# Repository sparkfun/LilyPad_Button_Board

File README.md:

SparkFun LilyPad Button Board
========================================

[*SparkFun LilyPad Button Board (DEV-08776)*](https://www.sparkfun.com/products/8776)

We designed this board to give the user a low profile button without any sharp edges. 
Button closes when you push it and opens when you release (momentary push button).

Repository Contents
-------------------
* **/Hardware** - All Eagle design files (.brd, .sch)

Documentation
-------------------
* **[Hookup Guide](https://learn.sparkfun.com/tutorials/lilypad-buttons-and-switches)**

License Information
-------------------

This product is _**open source**_! 

Please review the LICENSE.md file for license information. 

If you have any questions or concerns on licensing, please contact techsupport@sparkfun.com.

Distributed as-is; no warranty is given.

- Your friends at SparkFun.

_<COLLABORATION CREDIT>_

_Note: A portion of this sale is given back to Dr. Leah Buechley for continued development and education of e-textiles._

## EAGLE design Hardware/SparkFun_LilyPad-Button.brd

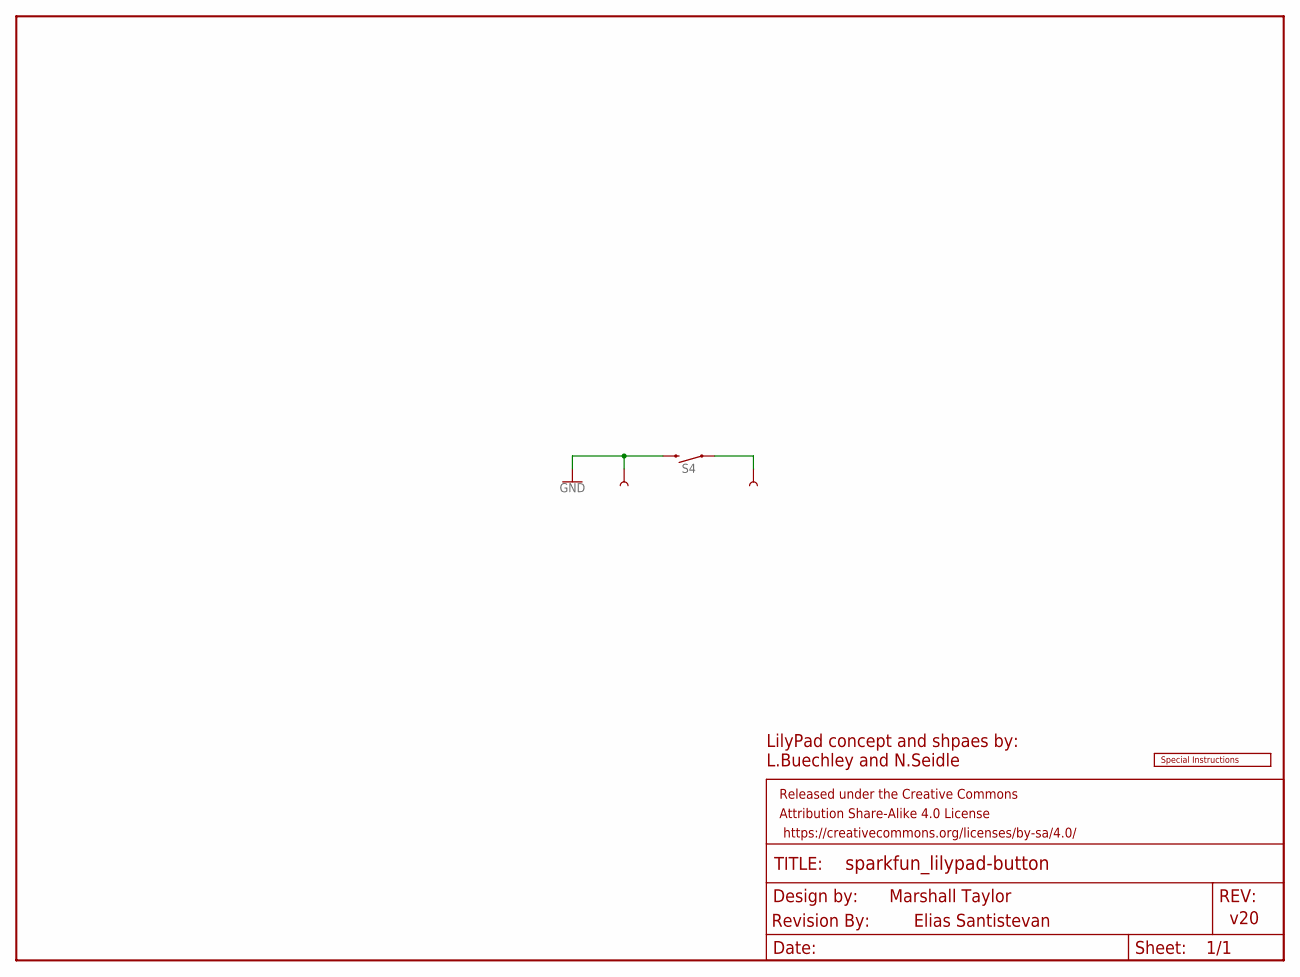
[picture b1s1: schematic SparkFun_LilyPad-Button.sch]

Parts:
FRAME2: FRAME-LETTER; CREATIVE_COMMONS
JP12, JP13: SEWTAP_MEDIUM-2SIDE; PETAL-MEDIUM-2SIDE
S4: MOMENTARY-SWITCH-SPST-SMD-5.2-REDUNDANT; TACTILE_SWITCH_SMD_5.2MM
U$1: SPECIAL_INSTRUCTIONS-ORDERING; ORDERING_INSTRUCTIONS

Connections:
D4: JP12.1, S4.1, S4.2 (1)
GND: JP13.1, S4.3 (2), S4.4 (2)

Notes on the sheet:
Marshall Taylor
v20
Elias Santistevan
Revision By:
LilyPad concept and shpaes by: L.Buechley and N.Seidle

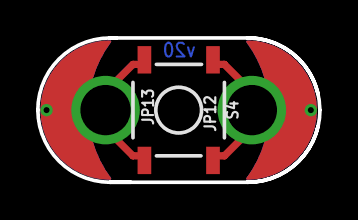
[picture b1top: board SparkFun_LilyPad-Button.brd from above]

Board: 2 copper layers, 15.7 x 8.0 mm, 6 parts (1 on the bottom side), 2 nets.

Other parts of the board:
U$45: LOGO-L

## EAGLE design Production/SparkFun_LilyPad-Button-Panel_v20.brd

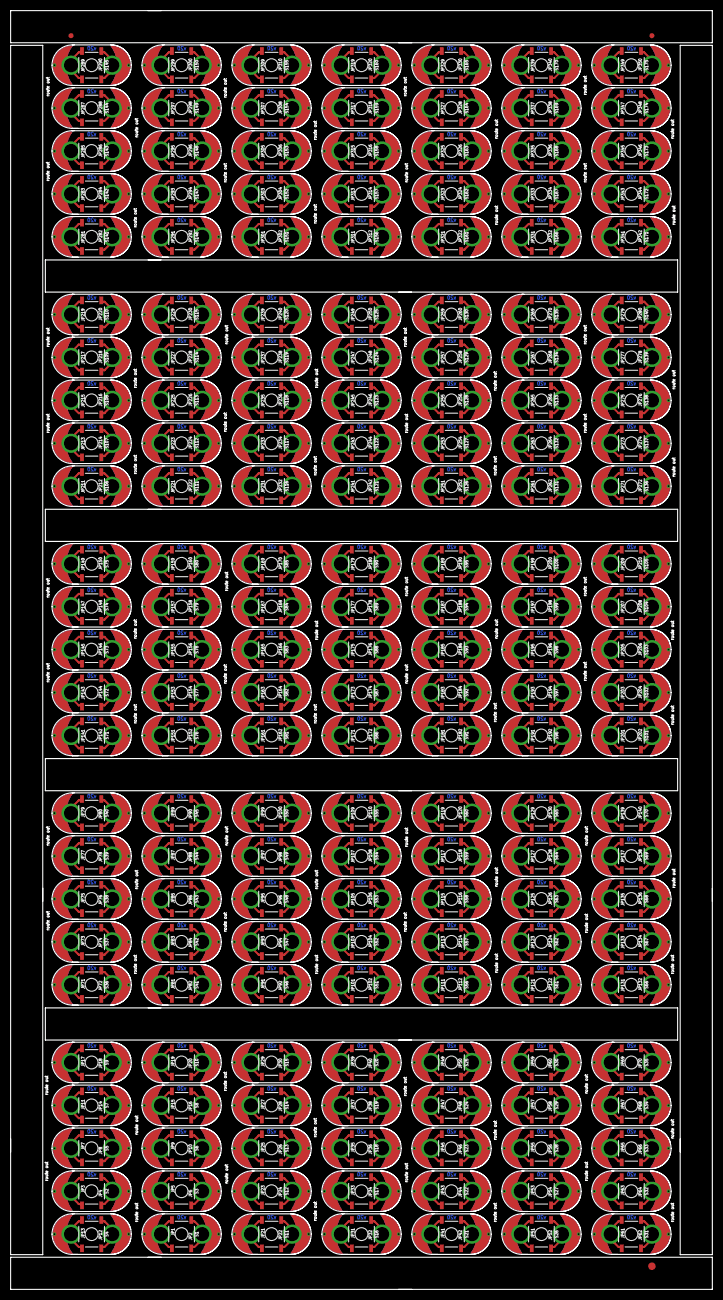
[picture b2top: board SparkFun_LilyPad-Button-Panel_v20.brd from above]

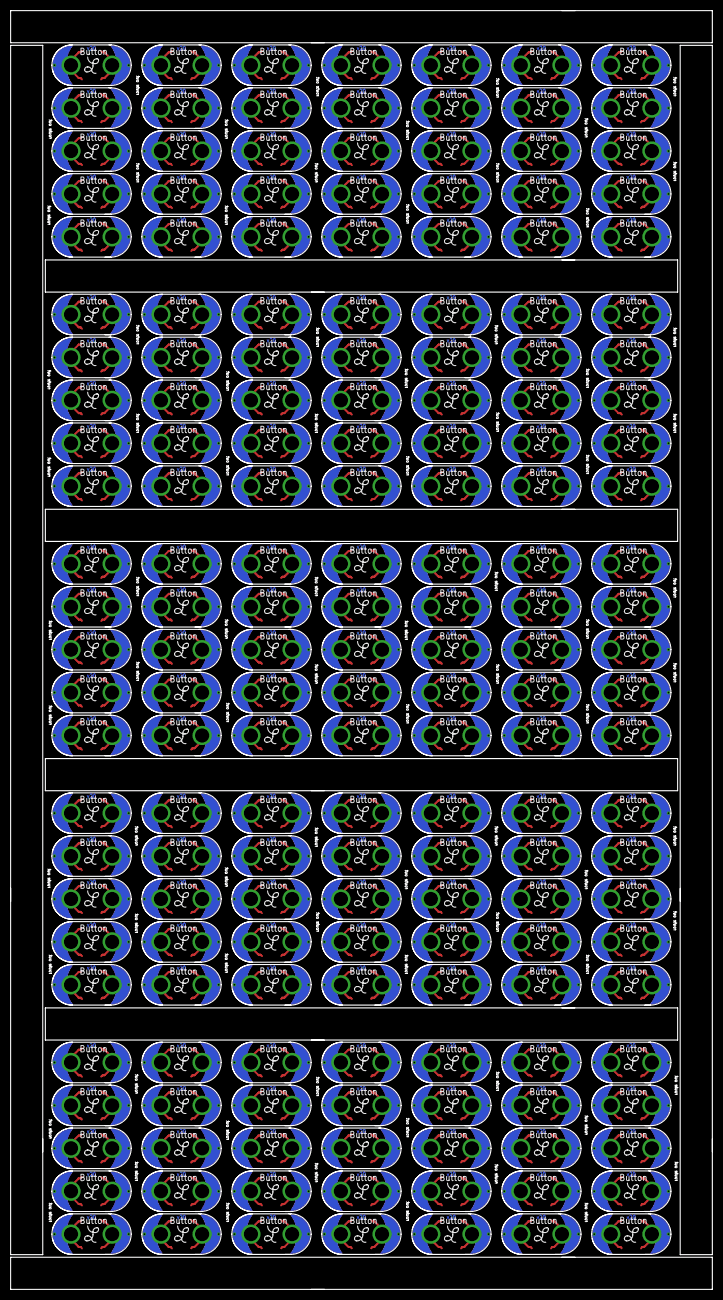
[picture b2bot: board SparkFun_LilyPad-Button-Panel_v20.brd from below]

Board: 2 copper layers, 138.7 x 252.7 mm, 703 parts (175 on the bottom side), 350 nets.

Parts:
E$1: FIDUCIAL-1.5X3
E$15, E$16: FIDUCIAL-1X2
JP1, JP2, JP3, JP4, JP5, JP6, JP7, JP8, JP9, JP10, JP11, JP12, JP13, JP14, JP15, JP16, JP17, JP18, JP19, JP20, JP21, JP22, JP23, JP24, JP25, JP26, JP27, JP28, JP29, JP30, JP31, JP32, JP33, JP34, JP35, JP36, JP37, JP38, JP39, JP40, JP41, JP42, JP43, JP44, JP45, JP46, JP47, JP48, JP49, JP50, JP51, JP52, JP53, JP54, JP55, JP56, JP57, JP58, JP59, JP60, JP61, JP62, JP63, JP64, JP65, JP66, JP67, JP68, JP69, JP70, JP71, JP72, JP73, JP74, JP75, JP76, JP77, JP78, JP79, JP80, JP81, JP82, JP83, JP84, JP85, JP86, JP87, JP88, JP89, JP90, JP91, JP92, JP93, JP94, JP95, JP96, JP97, JP98, JP99, JP100, JP101, JP102, JP103, JP104, JP105, JP106, JP107, JP108, JP109, JP110, JP111, JP112, JP113, JP114, JP115, JP116, JP117, JP118, JP119, JP120, JP121, JP122, JP123, JP124, JP125, JP126, JP127, JP128, JP129, JP130, JP131, JP132, JP133, JP134, JP135, JP136, JP137, JP138, JP139, JP140, JP141, JP142, JP143, JP144, JP145, JP146, JP147, JP148, JP149, JP150, JP151, JP152, JP153, JP154, JP155, JP156, JP157, JP158, JP159, JP160, JP161, JP162, JP163, JP164, JP165, JP166, JP167, JP168, JP169, JP170, JP171, JP172, JP173, JP174, JP175, JP176, JP177, JP178, JP179, JP180, JP181, JP182, JP183, JP184, JP185, JP186, JP187, JP188, JP189, JP190, JP191, JP192, JP193, JP194, JP195, JP196, JP197, JP198, JP199, JP200, JP201, JP202, JP203, JP204, JP205, JP206, JP207, JP208, JP209, JP210, JP211, JP212, JP213, JP214, JP215, JP216, JP217, JP218, JP219, JP220, JP221, JP222, JP223, JP224, JP225, JP226, JP227, JP228, JP229, JP230, JP231, JP232, JP233, JP234, JP235, JP236, JP237, JP238, JP239, JP240, JP241, JP242, JP243, JP244, JP245, JP246, JP247, JP248, JP249, JP250, JP251, JP252, JP253, JP254, JP255, JP256, JP257, JP258, JP259, JP260, JP261, JP262, JP263, JP264, JP265, JP266, JP267, JP268, JP269, JP270, JP271, JP272, JP273, JP274, JP275, JP276, JP277, JP278, JP279, JP280, JP281, JP282, JP283, JP284, JP285, JP286, JP287, JP288, JP289, JP290, JP291, JP292, JP293, JP294, JP295, JP296, JP297, JP298, JP299, JP300, JP301, JP302, JP303, JP304, JP305, JP306, JP307, JP308, JP309, JP310, JP311, JP312, JP313, JP314, JP315, JP316, JP317, JP318, JP319, JP320, JP321, JP322, JP323, JP324, JP325, JP326, JP327, JP328, JP329, JP330, JP331, JP332, JP333, JP334, JP335, JP336, JP337, JP338, JP339, JP340, JP341, JP342, JP343, JP344, JP345, JP346, JP347, JP348, JP349, JP350: SEWTAP_MEDIUM-2SIDE; PETAL-MEDIUM-2SIDE
S1, S2, S3, S4, S5, S6, S7, S8, S9, S10, S11, S12, S13, S14, S15, S16, S17, S18, S19, S20, S21, S22, S23, S24, S25, S26, S27, S28, S29, S30, S31, S32, S33, S34, S35, S36, S37, S38, S39, S40, S41, S42, S43, S44, S45, S46, S47, S48, S49, S50, S51, S52, S53, S54, S55, S56, S57, S58, S59, S60, S61, S62, S63, S64, S65, S66, S67, S68, S69, S70, S71, S72, S73, S74, S75, S76, S77, S78, S79, S80, S81, S82, S83, S84, S85, S86, S87, S88, S89, S90, S91, S92, S93, S94, S95, S96, S97, S98, S99, S100, S101, S102, S103, S104, S105, S106, S107, S108, S109, S110, S111, S112, S113, S114, S115, S116, S117, S118, S119, S120, S121, S122, S123, S124, S125, S126, S127, S128, S129, S130, S131, S132, S133, S134, S135, S136, S137, S138, S139, S140, S141, S142, S143, S144, S145, S146, S147, S148, S149, S150, S151, S152, S153, S154, S155, S156, S157, S158, S159, S160, S161, S162, S163, S164, S165, S166, S167, S168, S169, S170, S171, S172, S173, S174, S175: MOMENTARY-SWITCH-SPST-SMD-5.2-REDUNDANT; TACTILE_SWITCH_SMD_5.2MM
U$1, U$2, U$3, U$4, U$5, U$6, U$7, U$8, U$9, U$10, U$11, U$12, U$13, U$14, U$15, U$16, U$17, U$18, U$19, U$20, U$21, U$22, U$23, U$24, U$25, U$26, U$27, U$28, U$29, U$30, U$31, U$32, U$33, U$34, U$35, U$36, U$37, U$38, U$39, U$40, U$41, U$42, U$43, U$44, U$45, U$46, U$47, U$48, U$49, U$50, U$51, U$52, U$53, U$54, U$55, U$56, U$57, U$58, U$59, U$60, U$61, U$62, U$63, U$64, U$65, U$66, U$67, U$68, U$69, U$70, U$71, U$72, U$73, U$74, U$75, U$76, U$77, U$78, U$79, U$80, U$81, U$82, U$83, U$84, U$85, U$86, U$87, U$88, U$89, U$90, U$91, U$92, U$93, U$94, U$95, U$96, U$97, U$98, U$99, U$100, U$101, U$102, U$103, U$104, U$105, U$106, U$107, U$108, U$109, U$110, U$111, U$112, U$113, U$114, U$115, U$116, U$117, U$118, U$119, U$120, U$121, U$122, U$123, U$124, U$125, U$126, U$127, U$128, U$129, U$130, U$131, U$132, U$133, U$134, U$135, U$136, U$137, U$138, U$139, U$140, U$141, U$142, U$143, U$144, U$145, U$146, U$147, U$148, U$149, U$150, U$151, U$152, U$153, U$154, U$155, U$156, U$157, U$158, U$159, U$160, U$161, U$162, U$163, U$164, U$165, U$166, U$167, U$168, U$169, U$170, U$171, U$172, U$173, U$174, U$175: LOGO-L

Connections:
D1: JP2.1, S1.1, S1.2
D2: JP4.1, S2.1, S2.2
D3: JP6.1, S3.1, S3.2
D4: JP12.1, S4.1, S4.2
D5: JP8.1, S5.1, S5.2
D6: JP10.1, S6.1, S6.2
D7: JP14.1, S7.1, S7.2
D8: JP16.1, S8.1, S8.2
D9: JP18.1, S9.1, S9.2
D10: JP20.1, S10.1, S10.2
D11: JP22.1, S11.1, S11.2
D12: JP24.1, S12.1, S12.2
D13: JP26.1, S13.1, S13.2
D14: JP28.1, S14.1, S14.2
D15: JP30.1, S15.1, S15.2
D16: JP32.1, S16.1, S16.2
D17: JP34.1, S17.1, S17.2
D18: JP36.1, S18.1, S18.2
D19: JP38.1, S19.1, S19.2
D20: JP40.1, S20.1, S20.2
D21: JP42.1, S21.1, S21.2
D22: JP44.1, S22.1, S22.2
D23: JP46.1, S23.1, S23.2
D24: JP48.1, S24.1, S24.2
D25: JP50.1, S25.1, S25.2
D26: JP52.1, S26.1, S26.2
D27: JP54.1, S27.1, S27.2
D28: JP56.1, S28.1, S28.2
D29: JP58.1, S29.1, S29.2
D30: JP60.1, S30.1, S30.2
D31: JP62.1, S31.1, S31.2
D32: JP64.1, S32.1, S32.2
D33: JP66.1, S33.1, S33.2
D34: JP68.1, S34.1, S34.2
D35: JP70.1, S35.1, S35.2
D36: JP72.1, S36.1, S36.2
D37: JP74.1, S37.1, S37.2
D38: JP76.1, S38.1, S38.2
D39: JP78.1, S39.1, S39.2
D40: JP80.1, S40.1, S40.2
D41: JP82.1, S41.1, S41.2
D42: JP84.1, S42.1, S42.2
D43: JP86.1, S43.1, S43.2
D44: JP88.1, S44.1, S44.2
D45: JP90.1, S45.1, S45.2
D46: JP92.1, S46.1, S46.2
D47: JP94.1, S47.1, S47.2
D48: JP96.1, S48.1, S48.2
D49: JP98.1, S49.1, S49.2
D50: JP100.1, S50.1, S50.2
D51: JP102.1, S51.1, S51.2
D52: JP104.1, S52.1, S52.2
D53: JP106.1, S53.1, S53.2
D54: JP108.1, S54.1, S54.2
D55: JP110.1, S55.1, S55.2
D56: JP112.1, S56.1, S56.2
D57: JP114.1, S57.1, S57.2
D58: JP116.1, S58.1, S58.2
D59: JP118.1, S59.1, S59.2
D60: JP120.1, S60.1, S60.2
D61: JP122.1, S61.1, S61.2
D62: JP124.1, S62.1, S62.2
D63: JP126.1, S63.1, S63.2
D64: JP128.1, S64.1, S64.2
D65: JP130.1, S65.1, S65.2
D66: JP132.1, S66.1, S66.2
D67: JP134.1, S67.1, S67.2
D68: JP136.1, S68.1, S68.2
D69: JP138.1, S69.1, S69.2
D70: JP140.1, S70.1, S70.2
D71: JP142.1, S71.1, S71.2
D72: JP144.1, S72.1, S72.2
D73: JP146.1, S73.1, S73.2
D74: JP148.1, S74.1, S74.2
D75: JP150.1, S75.1, S75.2
D76: JP152.1, S76.1, S76.2
D77: JP154.1, S77.1, S77.2
D78: JP156.1, S78.1, S78.2
D79: JP158.1, S79.1, S79.2
D80: JP160.1, S80.1, S80.2
D81: JP162.1, S81.1, S81.2
D82: JP164.1, S82.1, S82.2
D83: JP166.1, S83.1, S83.2
D84: JP168.1, S84.1, S84.2
D85: JP170.1, S85.1, S85.2
D86: JP172.1, S86.1, S86.2
D87: JP174.1, S87.1, S87.2
D88: JP176.1, S88.1, S88.2
D89: JP178.1, S89.1, S89.2
D90: JP180.1, S90.1, S90.2
D91: JP182.1, S91.1, S91.2
D92: JP184.1, S92.1, S92.2
D93: JP186.1, S93.1, S93.2
D94: JP188.1, S94.1, S94.2
D95: JP190.1, S95.1, S95.2
D96: JP192.1, S96.1, S96.2
D97: JP194.1, S97.1, S97.2
D98: JP196.1, S98.1, S98.2
D99: JP198.1, S99.1, S99.2
D100: JP200.1, S100.1, S100.2
D101: JP202.1, S101.1, S101.2
D102: JP204.1, S102.1, S102.2
D103: JP206.1, S103.1, S103.2
D104: JP208.1, S104.1, S104.2
D105: JP210.1, S105.1, S105.2
D106: JP212.1, S106.1, S106.2
D107: JP214.1, S107.1, S107.2
D108: JP216.1, S108.1, S108.2
D109: JP218.1, S109.1, S109.2
D110: JP220.1, S110.1, S110.2
D111: JP222.1, S111.1, S111.2
D112: JP224.1, S112.1, S112.2
D113: JP226.1, S113.1, S113.2
D114: JP228.1, S114.1, S114.2
D115: JP230.1, S115.1, S115.2
D116: JP232.1, S116.1, S116.2
D117: JP234.1, S117.1, S117.2
D118: JP236.1, S118.1, S118.2
D119: JP238.1, S119.1, S119.2
D120: JP240.1, S120.1, S120.2
D121: JP242.1, S121.1, S121.2
D122: JP244.1, S122.1, S122.2
D123: JP246.1, S123.1, S123.2
D124: JP248.1, S124.1, S124.2
D125: JP250.1, S125.1, S125.2
D126: JP252.1, S126.1, S126.2
D127: JP254.1, S127.1, S127.2
D128: JP256.1, S128.1, S128.2
D129: JP258.1, S129.1, S129.2
D130: JP260.1, S130.1, S130.2
D131: JP262.1, S131.1, S131.2
D132: JP264.1, S132.1, S132.2
D133: JP266.1, S133.1, S133.2
D134: JP268.1, S134.1, S134.2
D135: JP270.1, S135.1, S135.2
D136: JP272.1, S136.1, S136.2
D137: JP274.1, S137.1, S137.2
D138: JP276.1, S138.1, S138.2
D139: JP278.1, S139.1, S139.2
D140: JP280.1, S140.1, S140.2
D141: JP282.1, S141.1, S141.2
D142: JP284.1, S142.1, S142.2
D143: JP286.1, S143.1, S143.2
D144: JP288.1, S144.1, S144.2
D145: JP290.1, S145.1, S145.2
D146: JP292.1, S146.1, S146.2
D147: JP294.1, S147.1, S147.2
D148: JP296.1, S148.1, S148.2
D149: JP298.1, S149.1, S149.2
D150: JP300.1, S150.1, S150.2
D151: JP302.1, S151.1, S151.2
D152: JP304.1, S152.1, S152.2
D153: JP306.1, S153.1, S153.2
D154: JP308.1, S154.1, S154.2
D155: JP310.1, S155.1, S155.2
D156: JP312.1, S156.1, S156.2
D157: JP314.1, S157.1, S157.2
D158: JP316.1, S158.1, S158.2
D159: JP318.1, S159.1, S159.2
D160: JP320.1, S160.1, S160.2
D161: JP322.1, S161.1, S161.2
D162: JP324.1, S162.1, S162.2
D163: JP326.1, S163.1, S163.2
D164: JP328.1, S164.1, S164.2
D165: JP330.1, S165.1, S165.2
D166: JP332.1, S166.1, S166.2
D167: JP334.1, S167.1, S167.2
D168: JP336.1, S168.1, S168.2
D169: JP338.1, S169.1, S169.2
D170: JP340.1, S170.1, S170.2
D171: JP342.1, S171.1, S171.2
D172: JP344.1, S172.1, S172.2
D173: JP346.1, S173.1, S173.2
D174: JP348.1, S174.1, S174.2
D175: JP350.1, S175.1, S175.2
GND: JP13.1, S4.3, S4.4
GND1: JP1.1, S1.3, S1.4
GND2: JP3.1, S2.3, S2.4
GND3: JP5.1, S3.3, S3.4
GND4: JP7.1, S5.3, S5.4
GND5: JP9.1, S6.3, S6.4
GND6: JP11.1, S7.3, S7.4
GND7: JP15.1, S8.3, S8.4
GND8: JP17.1, S9.3, S9.4
GND9: JP19.1, S10.3, S10.4
GND10: JP21.1, S11.3, S11.4
GND11: JP23.1, S12.3, S12.4
GND12: JP25.1, S13.3, S13.4
GND13: JP27.1, S14.3, S14.4
GND14: JP29.1, S15.3, S15.4
GND15: JP31.1, S16.3, S16.4
GND16: JP33.1, S17.3, S17.4
GND17: JP35.1, S18.3, S18.4
GND18: JP37.1, S19.3, S19.4
GND19: JP39.1, S20.3, S20.4
GND20: JP41.1, S21.3, S21.4
GND21: JP43.1, S22.3, S22.4
GND22: JP45.1, S23.3, S23.4
GND23: JP47.1, S24.3, S24.4
GND24: JP49.1, S25.3, S25.4
GND25: JP51.1, S26.3, S26.4
GND26: JP53.1, S27.3, S27.4
GND27: JP55.1, S28.3, S28.4
GND28: JP57.1, S29.3, S29.4
GND29: JP59.1, S30.3, S30.4
GND30: JP61.1, S31.3, S31.4
GND31: JP63.1, S32.3, S32.4
GND32: JP65.1, S33.3, S33.4
GND33: JP67.1, S34.3, S34.4
GND34: JP69.1, S35.3, S35.4
GND35: JP71.1, S36.3, S36.4
GND36: JP73.1, S37.3, S37.4
GND37: JP75.1, S38.3, S38.4
GND38: JP77.1, S39.3, S39.4
GND39: JP79.1, S40.3, S40.4
GND40: JP81.1, S41.3, S41.4
GND41: JP83.1, S42.3, S42.4
GND42: JP85.1, S43.3, S43.4
GND43: JP87.1, S44.3, S44.4
GND44: JP89.1, S45.3, S45.4
GND45: JP91.1, S46.3, S46.4
GND46: JP93.1, S47.3, S47.4
GND47: JP95.1, S48.3, S48.4
GND48: JP97.1, S49.3, S49.4
GND49: JP99.1, S50.3, S50.4
GND50: JP101.1, S51.3, S51.4
GND51: JP103.1, S52.3, S52.4
GND52: JP105.1, S53.3, S53.4
GND53: JP107.1, S54.3, S54.4
GND54: JP109.1, S55.3, S55.4
GND55: JP111.1, S56.3, S56.4
GND56: JP113.1, S57.3, S57.4
GND57: JP115.1, S58.3, S58.4
GND58: JP117.1, S59.3, S59.4
GND59: JP119.1, S60.3, S60.4
GND60: JP121.1, S61.3, S61.4
GND61: JP123.1, S62.3, S62.4
GND62: JP125.1, S63.3, S63.4
GND63: JP127.1, S64.3, S64.4
GND64: JP129.1, S65.3, S65.4
GND65: JP131.1, S66.3, S66.4
GND66: JP133.1, S67.3, S67.4
GND67: JP135.1, S68.3, S68.4
GND68: JP137.1, S69.3, S69.4
GND69: JP139.1, S70.3, S70.4
GND70: JP141.1, S71.3, S71.4
GND71: JP143.1, S72.3, S72.4
GND72: JP145.1, S73.3, S73.4
GND73: JP147.1, S74.3, S74.4
GND74: JP149.1, S75.3, S75.4
GND75: JP151.1, S76.3, S76.4
GND76: JP153.1, S77.3, S77.4
GND77: JP155.1, S78.3, S78.4
GND78: JP157.1, S79.3, S79.4
GND79: JP159.1, S80.3, S80.4
GND80: JP161.1, S81.3, S81.4
GND81: JP163.1, S82.3, S82.4
GND82: JP165.1, S83.3, S83.4
GND83: JP167.1, S84.3, S84.4
GND84: JP169.1, S85.3, S85.4
GND85: JP171.1, S86.3, S86.4
GND86: JP173.1, S87.3, S87.4
GND87: JP175.1, S88.3, S88.4
GND88: JP177.1, S89.3, S89.4
GND89: JP179.1, S90.3, S90.4
GND90: JP181.1, S91.3, S91.4
GND91: JP183.1, S92.3, S92.4
GND92: JP185.1, S93.3, S93.4
GND93: JP187.1, S94.3, S94.4
GND94: JP189.1, S95.3, S95.4
GND95: JP191.1, S96.3, S96.4
GND96: JP193.1, S97.3, S97.4
GND97: JP195.1, S98.3, S98.4
GND98: JP197.1, S99.3, S99.4
GND99: JP199.1, S100.3, S100.4
GND100: JP201.1, S101.3, S101.4
GND101: JP203.1, S102.3, S102.4
GND102: JP205.1, S103.3, S103.4
GND103: JP207.1, S104.3, S104.4
GND104: JP209.1, S105.3, S105.4
GND105: JP211.1, S106.3, S106.4
GND106: JP213.1, S107.3, S107.4
GND107: JP215.1, S108.3, S108.4
GND108: JP217.1, S109.3, S109.4
GND109: JP219.1, S110.3, S110.4
GND110: JP221.1, S111.3, S111.4
GND111: JP223.1, S112.3, S112.4
GND112: JP225.1, S113.3, S113.4
GND113: JP227.1, S114.3, S114.4
GND114: JP229.1, S115.3, S115.4
GND115: JP231.1, S116.3, S116.4
GND116: JP233.1, S117.3, S117.4
GND117: JP235.1, S118.3, S118.4
GND118: JP237.1, S119.3, S119.4
GND119: JP239.1, S120.3, S120.4
GND120: JP241.1, S121.3, S121.4
GND121: JP243.1, S122.3, S122.4
GND122: JP245.1, S123.3, S123.4
GND123: JP247.1, S124.3, S124.4
GND124: JP249.1, S125.3, S125.4
GND125: JP251.1, S126.3, S126.4
GND126: JP253.1, S127.3, S127.4
GND127: JP255.1, S128.3, S128.4
GND128: JP257.1, S129.3, S129.4
GND129: JP259.1, S130.3, S130.4
GND130: JP261.1, S131.3, S131.4
GND131: JP263.1, S132.3, S132.4
GND132: JP265.1, S133.3, S133.4
GND133: JP267.1, S134.3, S134.4
GND134: JP269.1, S135.3, S135.4
GND135: JP271.1, S136.3, S136.4
GND136: JP273.1, S137.3, S137.4
GND137: JP275.1, S138.3, S138.4
GND138: JP277.1, S139.3, S139.4
GND139: JP279.1, S140.3, S140.4
GND140: JP281.1, S141.3, S141.4
GND141: JP283.1, S142.3, S142.4
GND142: JP285.1, S143.3, S143.4
GND143: JP287.1, S144.3, S144.4
GND144: JP289.1, S145.3, S145.4
GND145: JP291.1, S146.3, S146.4
GND146: JP293.1, S147.3, S147.4
GND147: JP295.1, S148.3, S148.4
GND148: JP297.1, S149.3, S149.4
GND149: JP299.1, S150.3, S150.4
GND150: JP301.1, S151.3, S151.4
GND151: JP303.1, S152.3, S152.4
GND152: JP305.1, S153.3, S153.4
GND153: JP307.1, S154.3, S154.4
GND154: JP309.1, S155.3, S155.4
GND155: JP311.1, S156.3, S156.4
GND156: JP313.1, S157.3, S157.4
GND157: JP315.1, S158.3, S158.4
GND158: JP317.1, S159.3, S159.4
GND159: JP319.1, S160.3, S160.4
GND160: JP321.1, S161.3, S161.4
GND161: JP323.1, S162.3, S162.4
GND162: JP325.1, S163.3, S163.4
GND163: JP327.1, S164.3, S164.4
GND164: JP329.1, S165.3, S165.4
GND165: JP331.1, S166.3, S166.4
GND166: JP333.1, S167.3, S167.4
GND167: JP335.1, S168.3, S168.4
GND168: JP337.1, S169.3, S169.4
GND169: JP339.1, S170.3, S170.4
GND170: JP341.1, S171.3, S171.4
GND171: JP343.1, S172.3, S172.4
GND172: JP345.1, S173.3, S173.4
GND173: JP347.1, S174.3, S174.4
GND174: JP349.1, S175.3, S175.4

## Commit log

2015-02-05 Initial hardware file commit
2018-02-08 Updated Special Ordering Instructions
2018-02-12 Clean up a few things
    Ready for review
2018-02-28 Changed to v20
2018-02-28 created panel v20
2018-04-24 Super fine adjustment of text
2018-06-08 One last adjustment of text
2018-06-11 updated v20 panel with new silk

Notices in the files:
parts and their libraries:
SparkFun-Aesthetics: Licensing: CC v3.0 Share-Alike You are welcome to use this library for commercial purposes.
SparkFun-Aesthetics: Released under the Creative Commons Attribution Share-Alike 4.0 License
SparkFun-Aesthetics: https://creativecommons.org/licenses/by-sa/4.0
